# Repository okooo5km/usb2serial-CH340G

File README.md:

## USB2TTL-CH340G

这是采用CH340G芯片的USB转UART模块的KiCAD工程设计文件，同时可以作为Arduino下载器。

#### 目标功能

1. 通用的usb转uart功能
2. 为Arduino下载程序
3. 自由选择3.3V或5V供电和信号电平模式。
4. 电源LED指示、TX和RX的LED指示

#### 原理图

#### PCB

#### PCB的3D预览

#### 附：

[CH340](http://www.wch.cn/product/CH340.html) 是一个 USB 总线的转接芯片,实现 USB 转串口、USB 转 IrDA 红外或者 USB 转打印口，其中设计中采用的CH340G是一款只有USB转串口功能的芯片。

##### I. 芯片驱动

1. [windows驱动](http://www.wch.cn/download/CH341SER_ZIP.html)
2. [Mac OSX驱动](http://www.wch.cn/download/CH341SER_MAC_ZIP.html)
3. [Linux驱动](http://www.wch.cn/download/CH341SER_LINUX_ZIP.html)

##### II. 注意

电路完成焊接后，因为稳压二极管的性能误差，可能会造成输出的3.3V不准，电压低于3.2V时可能会造成Mac电脑在使用3.3V的工作模式时UART通信有问题。可以通过更换稳压二极管或者更小阻值的电阻R3来解决。

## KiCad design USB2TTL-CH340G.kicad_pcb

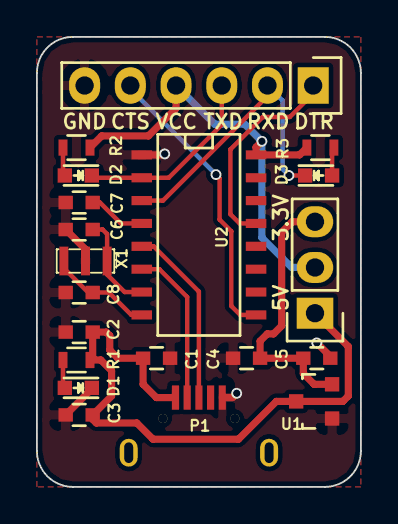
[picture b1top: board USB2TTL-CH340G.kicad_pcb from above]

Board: 2 copper layers, 18.0 x 25.0 mm, 20 parts (0 on the bottom side), 16 nets.

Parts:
C1: 10uF; C_0603
C2, C4: 0.1uF; C_0603
C3, C5: 1uF; C_0603
C6, C8: 22pF; C_0603
C7: 0.01uF; C_0603
D1: PWR; LED_0603
D2: TXD; LED_0603
D3: RXD; LED_0603
P1: USB_OTG; USB_Micro-B-MK5
P2: PWR_SEL; Pin_Header_Straight_1x03
P3: CONN_01X06; Pin_Header_Straight_1x06
R1, R2, R3: 4.7K; R_0603
U1: XC6206P332MR; SOT-23
U2: CH340G; SO-16-N
X1: CRYSTAL_SMD; Resonator_3.2x1.5mm

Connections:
+3.3V: C4.1, C5.1, P2.3, U1.2
+5V: C1.1, C2.1, C3.1, P1.1, P2.1, R1.2, U1.3
/CTS: P3.5, U2.9
/DTR: P3.1, U2.13
/RXD: D3.1, P3.2, U2.3
/TXD: D2.1, P3.3, U2.2
GND: C1.2, C2.2, C3.2, C4.2, C5.2, C6.2, C7.2, C8.2, D1.1, P1.5, P3.6, U1.1, U2.1, X1.3
unnamed: C6.1, U2.7, X1.1
unnamed: C7.1, U2.4
unnamed: C8.1, U2.8, X1.2
unnamed: D1.2, R1.1
unnamed: D2.2, R2.2
unnamed: D3.2, R3.2
unnamed: P1.2, U2.6
unnamed: P1.3, U2.5
VCC: P2.2, P3.4, R2.1, R3.1, U2.16

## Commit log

2016-06-12 添加版本v0.01的设计文件及相关的描述文件和图片
2016-06-12 更新为版本v0.2，修改内容如下：1.修复电源电路连接问题（v3和VCC）。2.重新布局使元件更紧凑，板型加入圆角。3.更改USB接口的封装。4.导出最新gerber及drill钻孔文件。
2016-06-13 更新bom，README添加芯片信息，修改忽略文件
2016-06-13 1.README中加入驱动链接及注意事项；2.更改R3电阻阻值为200欧姆；3.修改gitignore文件忽略bak文件。
2016-06-20 修改micro usb封装，添加定位孔，更新pcb封装
2016-07-31 删掉对外供电的插针，重新布局设计PCB，大小为25mmX18mm，并导出单板的gerber文件和钻孔文件
2016-07-31 更新README，并更新截图
2016-08-21 1.新建myRegul库并添加元件LDO芯片XP6206；2.用最大可提供500mA电流的XP6206替换掉原来的二极管稳压电路，提高稳定性；3.调整PCB元件布局。
2016-08-21 拼板导出相应gerber和drill文件
